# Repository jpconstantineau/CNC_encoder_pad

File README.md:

# CNC_encoder_pad
Wireless Video Editing Macropad and Jog Wheel

## What is it?

The CNC EncoderPad is a Video Editing Macropad with a 60mm Encoder Wheel that's designed for use for CNC machines. This encoder is made of metal and feels like it will last forever. The EncoderPad uses 9 mechanical switches (Cherry MX type). Each key has an individual LED which can be turned on. Since it uses a BlueMicro840, it uses a nRF52840 processor to handle all functions, including BLE.

## Why did I design it?

As I have been editing more videos for the BlueMicro Youtube Channel, I have been looking for a useful macropad that includes a jog wheel that can be re-programmed for various purposes. Since my BlueMicro firmware now supports rotary encoders , I was able to create a purpose-made video editing macropad that's fully programmable using the Arduino IDE.

## How do I program it?

If you are familiar with programming Arduinos or customizing the firmware of your mechanical keyboards programmatically (as opposed through automated online tools), you should find it easy. The firmware used is available on github. There are a number of tutorial videos on how to program the BlueMicro_BLE firmware as well as lots of documentation, examples and help to get going.

The hard part will be to find out what key bindings to use for your favorite software!

## How do I get one?

You can get a kit with all the parts you need on my Tindie store.  Just go to the product [page](https://www.tindie.com/products/jpconstantineau/wireless-video-editing-macropad-and-jog-wheel/) and you can order one.

## How do I build one?

Head over the [build guide](/BuildInstructions.md) to see all the details.

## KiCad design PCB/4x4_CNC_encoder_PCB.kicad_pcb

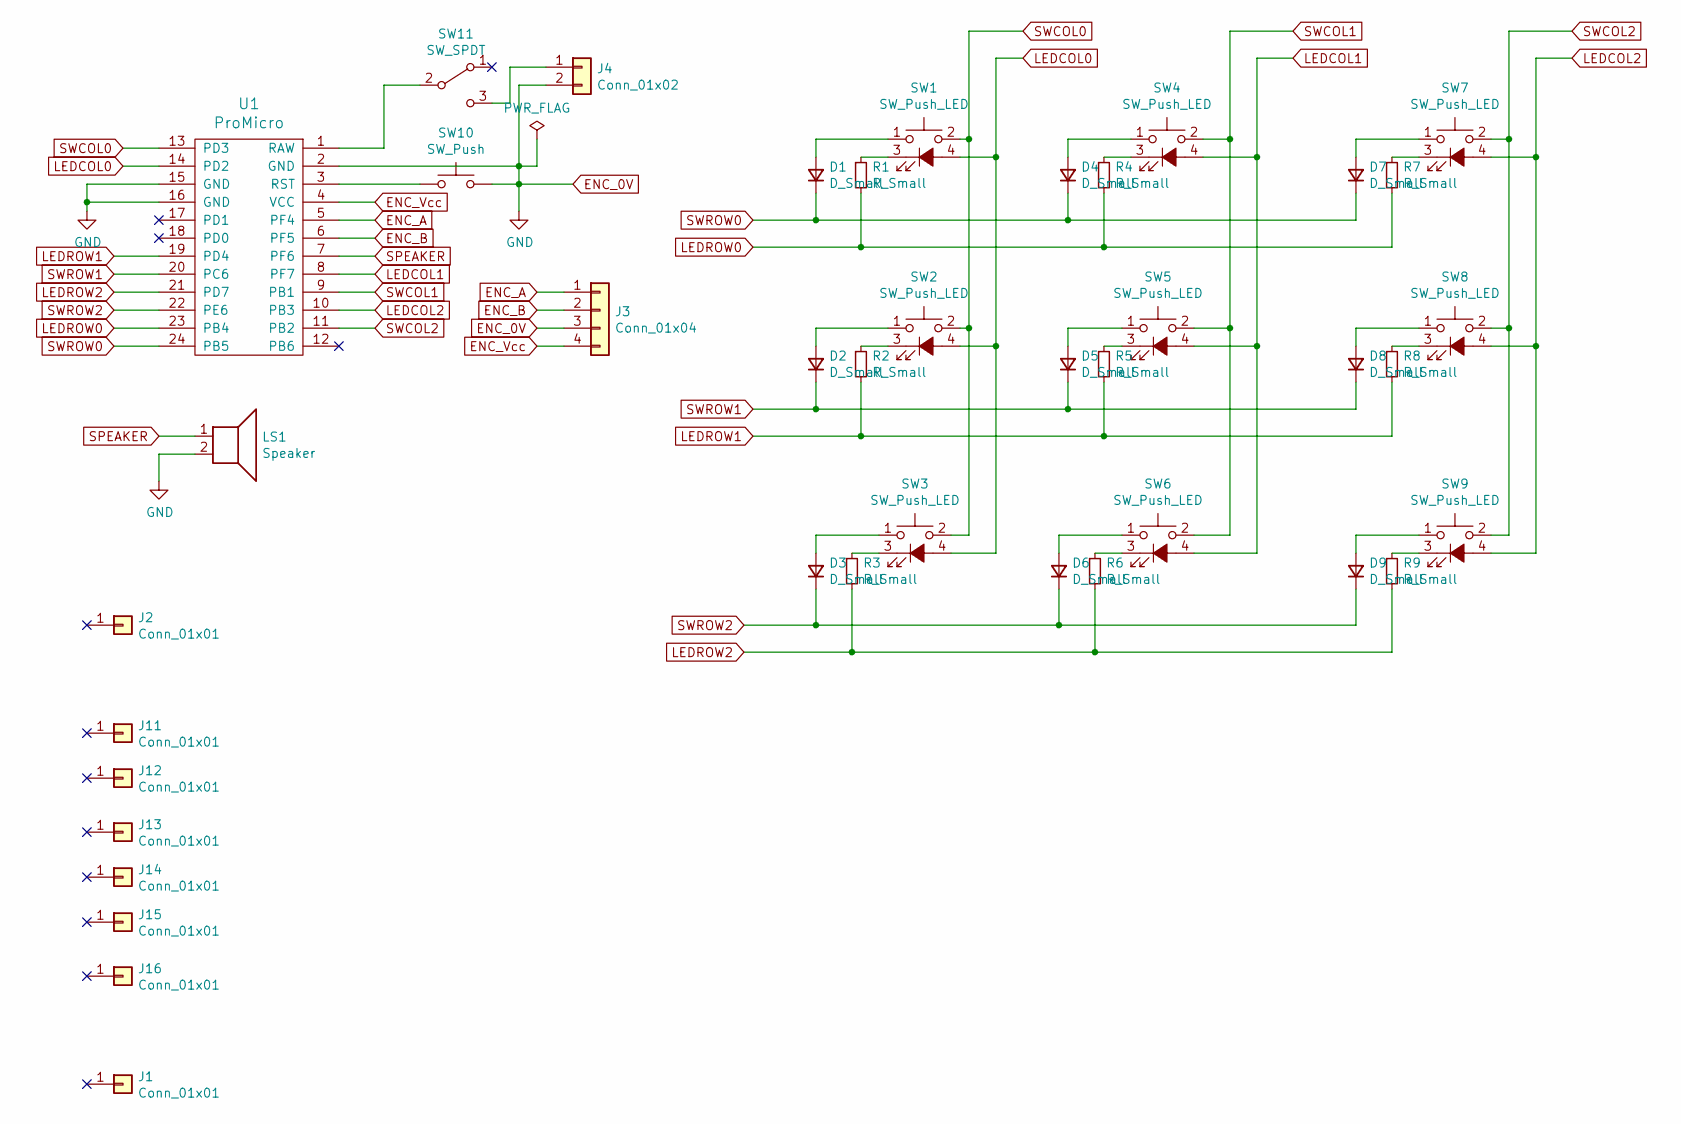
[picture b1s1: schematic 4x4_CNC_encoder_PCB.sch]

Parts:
D1, D2, D3, D4, D5, D6, D7, D8, D9: D_Small; D_DO-35_SOD27_P10.16mm_Horizontal
J1: Conn_01x01; CNC_Encoder
J2, J11, J12, J13, J14, J15, J16: Conn_01x01; MountingHole_3.5mm
J3: Conn_01x04; PinHeader_1x04_P2.54mm_Vertical
J4: Conn_01x02; PinHeader_1x02_P2.54mm_Vertical
LS1: Speaker; AST1109MLTRQ
R1, R2, R3, R4, R5, R6, R7, R8, R9: R_Small; R_Axial_DIN0207_L6.3mm_D2.5mm_P10.16mm_Horizontal
SW1, SW2, SW3, SW4, SW5, SW6, SW7, SW8, SW9: SW_Push_LED; MX-Alps-Choc-1U
SW10: SW_Push; SW_TACT_ALPS_SKQGABE010
SW11: SW_SPDT; SPDT_C128955
U1: ProMicro; Pro_Micro

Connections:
ENC_0V: J3.3, J4.2, LS1.2, SW10.2, U1.2 (GND), U1.15 (GND), U1.16 (GND)
ENC_A: J3.1, U1.5 (PF4)
ENC_B: J3.2, U1.6 (PF5)
ENC_Vcc: J3.4, U1.4 (VCC)
LEDCOL0: SW1.4 (A), SW2.4 (A), SW3.4 (A), U1.14 (PD2)
LEDCOL1: SW4.4 (A), SW5.4 (A), SW6.4 (A), U1.8 (PF7)
LEDCOL2: SW7.4 (A), SW8.4 (A), SW9.4 (A), U1.10 (PB3)
LEDROW0: R1.2, R4.2, R7.2, U1.23 (PB4)
LEDROW1: R2.2, R5.2, R8.2, U1.19 (PD4)
LEDROW2: R3.2, R6.2, R9.2, U1.21 (PD7)
unnamed: D1.2 (A), SW1.1
unnamed: D2.2 (A), SW2.1
unnamed: D3.2 (A), SW3.1
unnamed: D4.2 (A), SW4.1
unnamed: D5.2 (A), SW5.1
unnamed: D6.2 (A), SW6.1
unnamed: D7.2 (A), SW7.1
unnamed: D8.2 (A), SW8.1
unnamed: D9.2 (A), SW9.1
unnamed: J4.1, SW11.3 (C)
unnamed: R1.1, SW1.3 (K)
unnamed: R2.1, SW2.3 (K)
unnamed: R3.1, SW3.3 (K)
unnamed: R4.1, SW4.3 (K)
unnamed: R5.1, SW5.3 (K)
unnamed: R6.1, SW6.3 (K)
unnamed: R7.1, SW7.3 (K)
unnamed: R8.1, SW8.3 (K)
unnamed: R9.1, SW9.3 (K)
unnamed: SW10.1, U1.3 (RST)
unnamed: SW11.2 (B), U1.1 (RAW)
SPEAKER: LS1.1, U1.7 (PF6)
SWCOL0: SW1.2, SW2.2, SW3.2, U1.13 (PD3)
SWCOL1: SW4.2, SW5.2, SW6.2, U1.9 (PB1)
SWCOL2: SW7.2, SW8.2, SW9.2, U1.11 (PB2)
SWROW0: D1.1 (K), D4.1 (K), D7.1 (K), U1.24 (PB5)
SWROW1: D2.1 (K), D5.1 (K), D8.1 (K), U1.20 (PC6)
SWROW2: D3.1 (K), D6.1 (K), D9.1 (K), U1.22 (PE6)

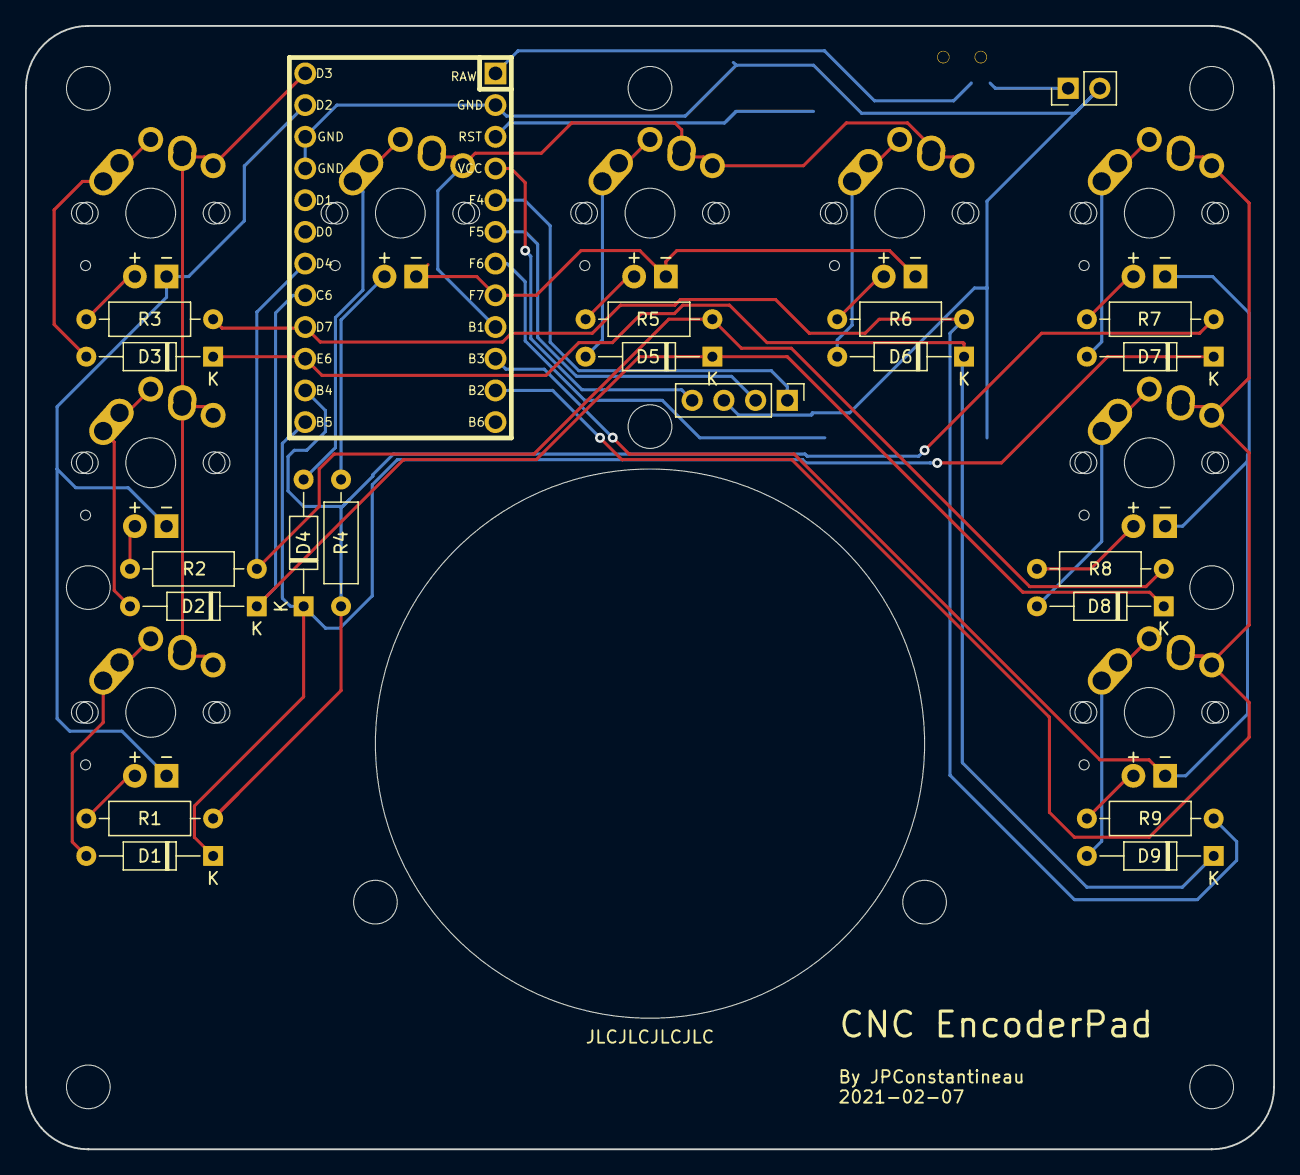
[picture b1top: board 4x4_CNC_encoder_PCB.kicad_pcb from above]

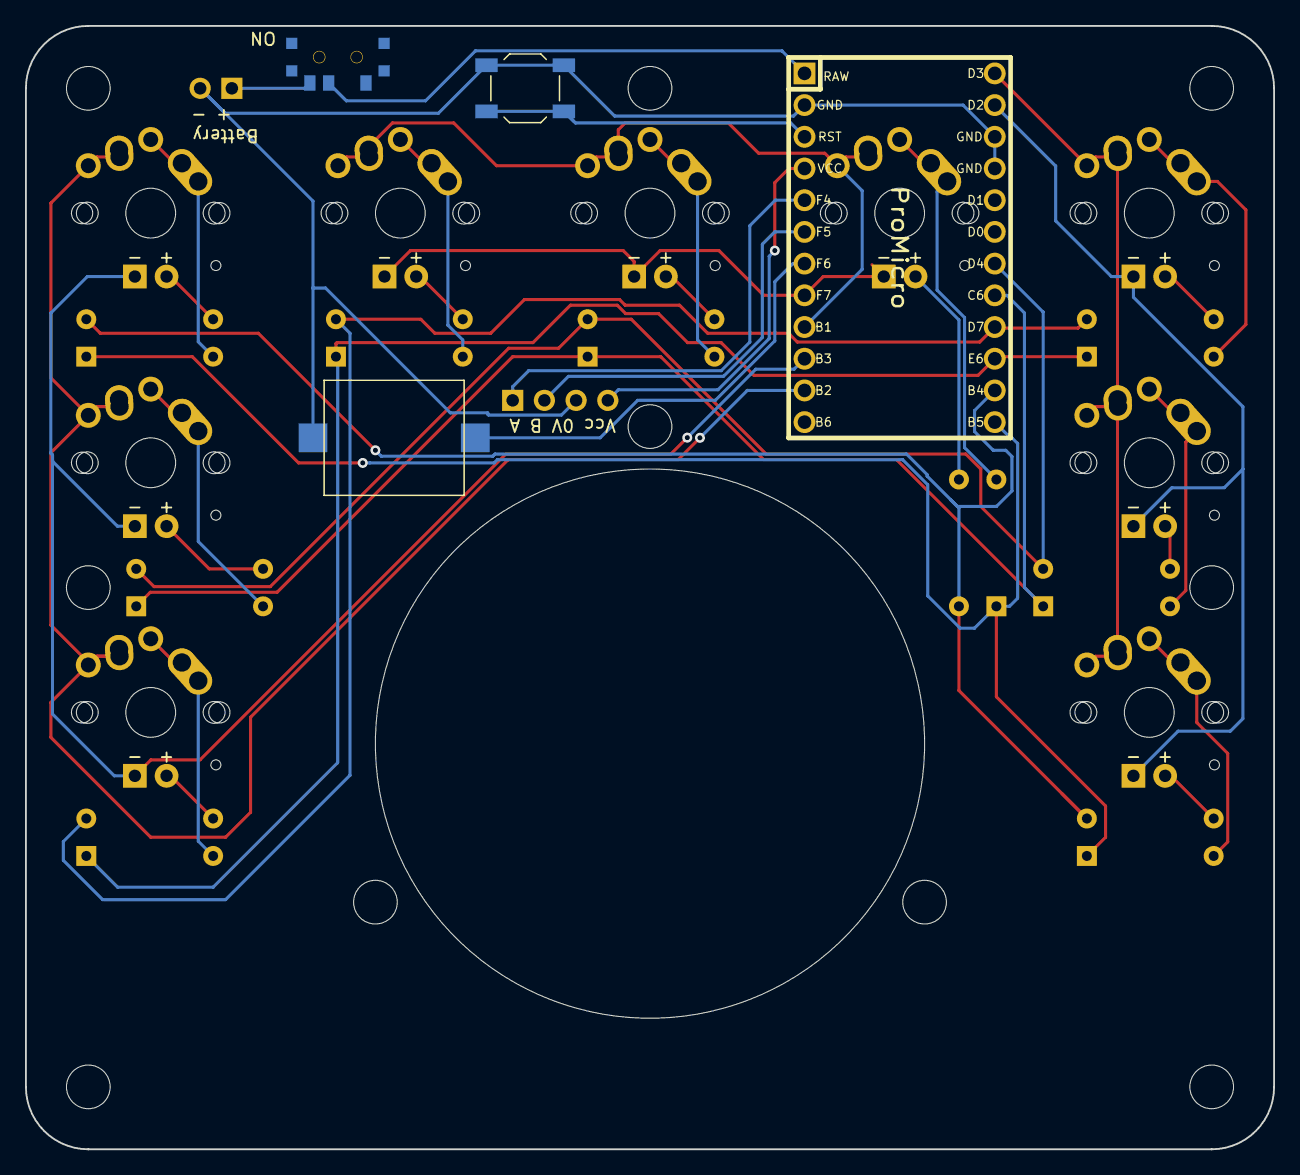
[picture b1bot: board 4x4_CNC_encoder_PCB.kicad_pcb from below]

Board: 2 copper layers, 100.0 x 90.0 mm, 41 parts (4 on the bottom side), 38 nets.

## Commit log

2021-04-30 start of docs
2021-05-30 update to build doc
2021-08-02 updated build guide
